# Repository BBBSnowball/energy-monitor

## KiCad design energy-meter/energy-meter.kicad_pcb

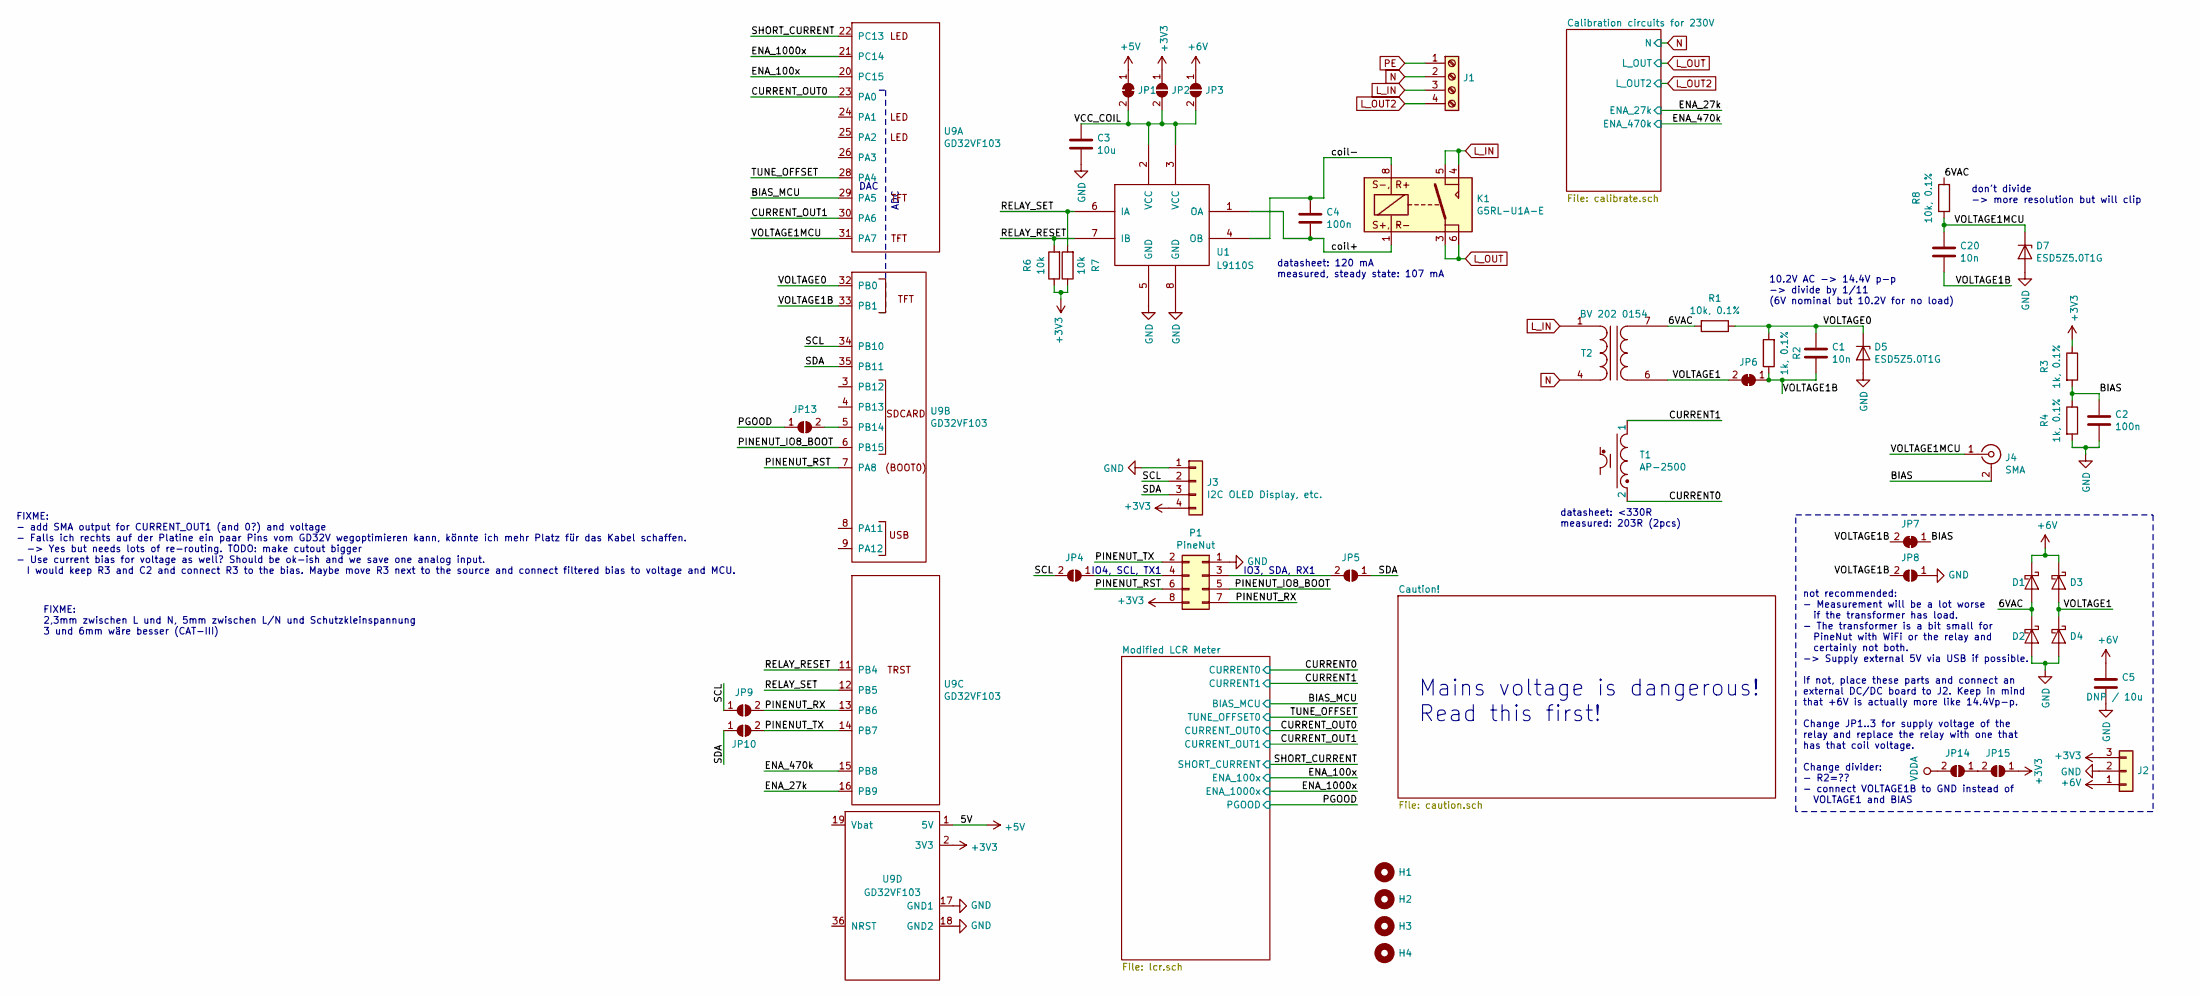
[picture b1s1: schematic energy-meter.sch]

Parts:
C1, C20: 10n; C_0603_1608Metric_Pad1.05x0.95mm_HandSolder
C2, C4: 100n; C_0603_1608Metric_Pad1.05x0.95mm_HandSolder
C3: 10u; C_0805_2012Metric_Pad1.15x1.40mm_HandSolder; LCSC CL21A106KOQNNNE
C5: DNP / 10u; C_0805_2012Metric_Pad1.15x1.40mm_HandSolder; LCSC CL21A106KOQNNNE
D1, D2, D3, D4: D_Schottky; D_SMA_Handsoldering; LCSC C181203, C364270, C50645
D5, D7: ESD5Z5.0T1G; D_SOD-523
H1, H2, H3, H4: MountingHole_3.2mm_M3; LCSC C63426, C357575, C357368, C357589
J1: Screw_Terminal_01x04; DG35C-B-04P-13-200AH
J2: Conn_01x03; PinHeader_1x03_P2.54mm_Horizontal
J3: I2C OLED Display, etc.; PinHeader_1x04_P2.54mm_Horizontal
J4: SMA; SMA_Samtec_SMA-J-P-H-ST-EM1_EdgeMount; LCSC C496550, C530661, (C1509221)
JP1, JP6, JP7: SolderJumper_2_Bridged; SolderJumper-2_P1.3mm_Bridged_RoundedPad1.0x1.5mm
JP2, JP3, JP4, JP5, JP8, JP9, JP10, JP13, JP14, JP15: SolderJumper_2_Open; SolderJumper-2_P1.3mm_Open_RoundedPad1.0x1.5mm
K1: G5RL-U1A-E
P1: PineNut; Pinenut-01S
R1, R8: 10k, 0.1%; R_0603_1608Metric_Pad1.05x0.95mm_HandSolder
R2, R3, R4: 1k, 0.1%; R_0603_1608Metric_Pad1.05x0.95mm_HandSolder
R6, R7: 10k; R_0603_1608Metric_Pad1.05x0.95mm_HandSolder
T1: AP-2500
T2: BV 202 0154; BV202
U1: L9110S; SOP-8_3.76x4.96mm_P1.27mm; LCSC C725793, C513306, C85174
U9: GD32VF103; GD32VF103CBT6-Sipeed-Longan-Nano

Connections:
+3V3: J2.3, J3.4, JP2.1 (A), JP15.1 (A), P1.8, R3.1, R6.1, R7.1, U9.2 (3V3); also elsewhere on the board
+5V: JP1.1 (A), U9.1 (5V); also elsewhere on the board
+6V: C5.1, D1.1 (K), D3.1 (K), J2.1, JP3.1 (A)
/6VAC: D1.2 (A), D2.1 (K), R1.2, R8.1, T2.7 (SB)
/BIAS: C2.1, J4.2 (Ext), JP7.1 (A), R3.2, R4.1
/BIAS_MCU: U9.29 (PA5); also elsewhere on the board
/CURRENT0: T1.2; also elsewhere on the board
/CURRENT1: T1.1; also elsewhere on the board
/CURRENT_OUT0: U9.23 (PA0); also elsewhere on the board
/CURRENT_OUT1: U9.30 (PA6); also elsewhere on the board
/ENA_27k: U9.16 (PB9); also elsewhere on the board
/ENA_100x: U9.20 (PC15); also elsewhere on the board
/ENA_470k: U9.15 (PB8); also elsewhere on the board
/ENA_1000x: U9.21 (PC14); also elsewhere on the board
/PGOOD: JP13.1 (A); also elsewhere on the board
/PINENUT_IO8_BOOT: P1.5, U9.6 (PB15)
/PINENUT_RST: P1.6, U9.7 (PA8)
/PINENUT_RX: JP9.2 (B), P1.7, U9.13 (PB6)
/PINENUT_TX: JP10.2 (B), P1.2, U9.14 (PB7)
/RELAY_RESET: R6.2, U1.7 (IB), U9.11 (PB4)
/RELAY_SET: R7.2, U1.6 (IA), U9.12 (PB5)
/SCL: J3.2, JP4.2 (B), JP9.1 (A), U9.34 (PB10); also elsewhere on the board
/SDA: J3.3, JP5.1 (A), JP10.1 (A), U9.35 (PB11); also elsewhere on the board
/SHORT_CURRENT: U9.22 (PC13); also elsewhere on the board
/TUNE_OFFSET: U9.28 (PA4); also elsewhere on the board
/VCC_COIL: C3.1, JP1.2 (B), JP2.2 (B), JP3.2 (B), U1.2 (VCC), U1.3 (VCC)
/VOLTAGE0: C1.1, D5.1 (K), R1.1, R2.2, U9.32 (PB0)
/VOLTAGE1: D3.2 (A), D4.1 (K), JP6.2 (B), T2.6 (SA)
/VOLTAGE1B: C1.2, C20.2, JP6.1 (A), JP7.2 (B), JP8.2 (B), R2.1, U9.33 (PB1)
/VOLTAGE1MCU: C20.1, D7.1 (K), J4.1 (In), R8.2, U9.31 (PA7)
/coil+: C4.2, K1.1, U1.1 (OA)
/coil-: C4.1, K1.8, U1.4 (OB)
GND: C2.2, C3.2, C5.2, D2.2 (A), D4.2 (A), D5.2 (A), D7.2 (A), J2.2, J3.1, JP8.1 (A), P1.1, R4.2, U1.5 (GND), U1.8 (GND), U9.17 (GND1), U9.18 (GND2); also elsewhere on the board
L_IN: J1.3, K1.4, K1.5, T2.1 (AA)
L_OUT: K1.3, K1.6; also elsewhere on the board
L_OUT2: J1.4; also elsewhere on the board
N: J1.2, T2.4 (AB); also elsewhere on the board
unnamed: JP4.1 (A), P1.4
unnamed: JP5.2 (B), P1.3
unnamed: JP13.2 (B), U9.5 (PB14)
unnamed: JP14.1 (A), JP15.2 (B)
PE: J1.1
VDDA: JP14.2 (B); also elsewhere on the board

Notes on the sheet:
ADC
IO3, SDA, RX1
IO4, SCL, TX1
10.2V AC -> 14.4V p-p -> divide by 1/11 (6V nominal but 10.2V for no load)
not recommended: - Measurement will be a lot worse if the transformer has load. - The transformer is a bit small for PineNut with WiFi or the relay and certainly not both. -> Supply external 5V via USB if possible. If not, place these parts and connect an external DC/DC board to J2. Keep in mind th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
DAC
datasheet: 120 mA measured, steady state: 107 mA
datasheet: <330R measured: 203R (2pcs)
Mains voltage is dangerous! Read this first!
don't divide -> more resolution but will clip
FIXME: - add SMA output for CURRENT_OUT1 (and 0?) and voltage - Falls ich rechts auf der Platine ein paar Pins vom GD32V wegoptimieren kann, könnte ich mehr Platz für das Kabel schaffen. -> Yes but needs lots of re-routing. TODO: make cutout bigger - Use current bias for voltage as well? Should be 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
FIXME: 2,3mm zwischen L und N, 5mm zwischen L/N und Schutzkleinspannung 3 und 6mm wäre besser (CAT-III)

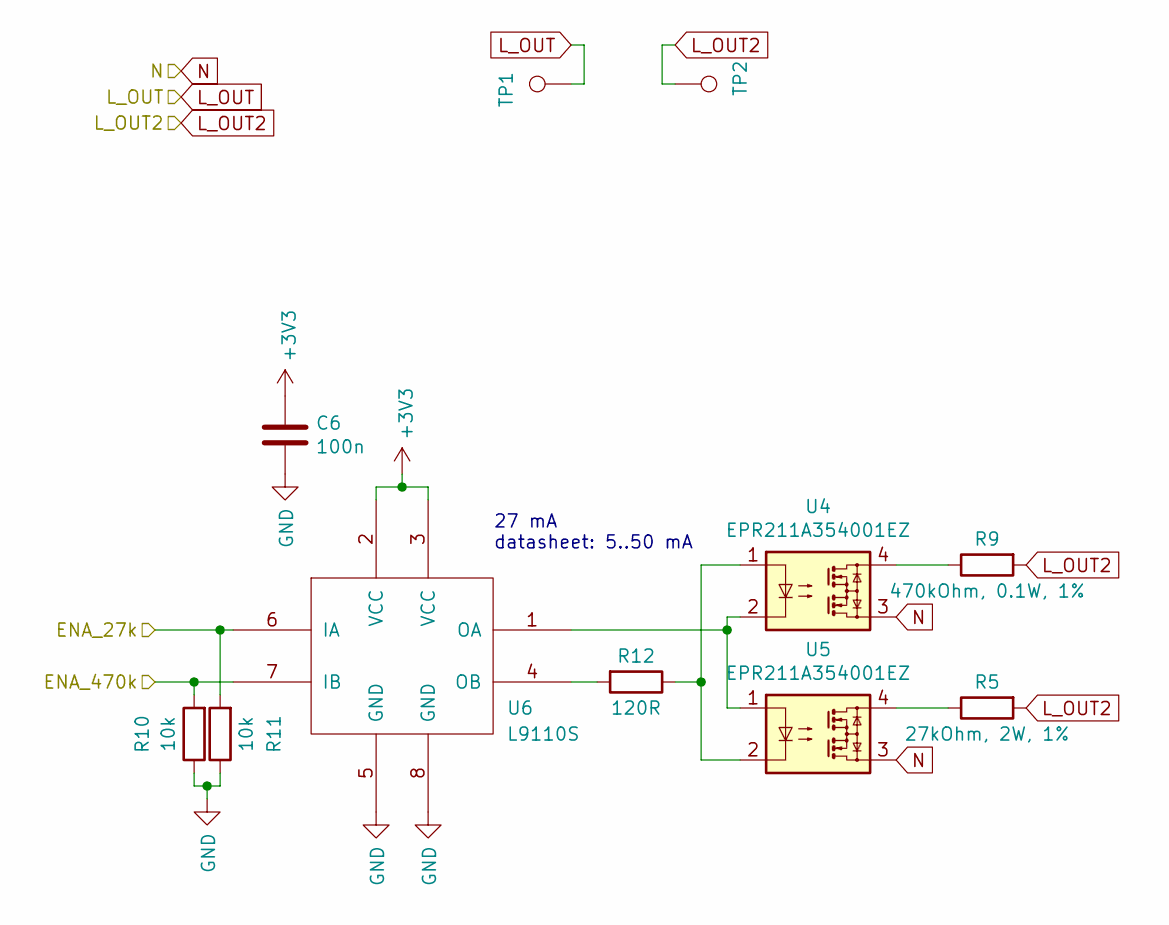
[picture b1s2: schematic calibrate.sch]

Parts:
C6: 100n; C_0603_1608Metric_Pad1.05x0.95mm_HandSolder
R5: 27kOhm, 2W, 1%; R_2512_6332Metric_Pad1.52x3.35mm_HandSolder
R9: 470kOhm, 0.1W, 1%; R_2512_6332Metric_Pad1.52x3.35mm_HandSolder
R10, R11: 10k; R_0603_1608Metric_Pad1.05x0.95mm_HandSolder
R12: 120R; R_0603_1608Metric_Pad1.05x0.95mm_HandSolder
TP1, TP2: TestPoint; TestPoint_THTPad_D4.0mm_Drill2.0mm
U4, U5: EPR211A354001EZ; DIP-4_W7.62mm
U6: L9110S; SOP-8_3.76x4.96mm_P1.27mm; LCSC C725793, C513306, C85174

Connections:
+3V3: C6.1, U6.2 (VCC), U6.3 (VCC); also elsewhere on the board
/ENA_27k: R11.2, U6.6 (IA); also elsewhere on the board
/ENA_470k: R10.2, U6.7 (IB); also elsewhere on the board
GND: C6.2, R10.1, R11.1, U6.5 (GND), U6.8 (GND); also elsewhere on the board
L_OUT: TP1.1; also elsewhere on the board
L_OUT2: R5.2, R9.2, TP2.1; also elsewhere on the board
N: U4.3, U5.3; also elsewhere on the board
unnamed: R5.1, U5.4
unnamed: R9.1, U4.4
unnamed: R12.1, U4.1, U5.2
unnamed: R12.2, U6.4 (OB)
unnamed: U4.2, U5.1, U6.1 (OA)

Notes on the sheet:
27 mA datasheet: 5..50 mA

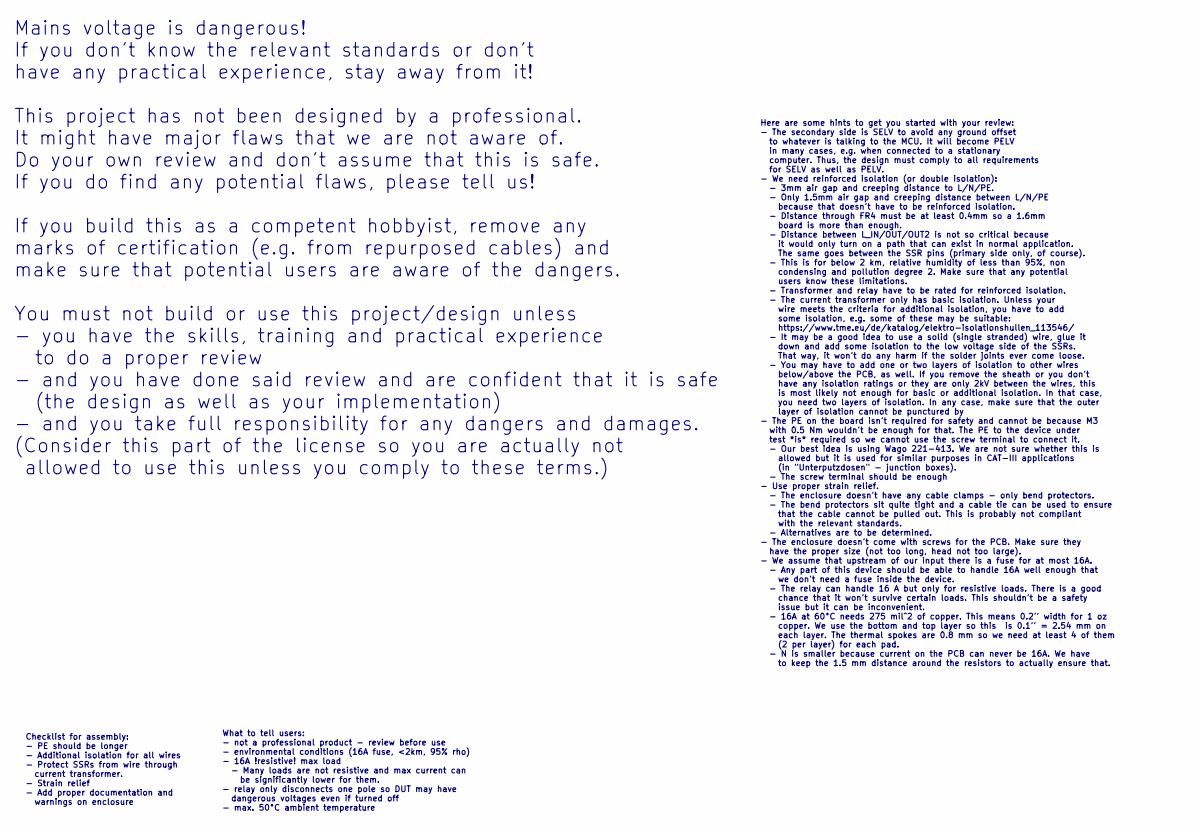
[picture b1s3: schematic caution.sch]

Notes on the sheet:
Mains voltage is dangerous! If you don't know the relevant standards or don't have any practical experience, stay away from it! This project has not been designed by a professional. It might have major flaws that we are not aware of. Do your own review and don't assume that this is safe. If you do 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
Here are some hints to get you started with your review: - The secondary side is SELV to avoid any ground offset to whatever is talking to the MCU. It will become PELV in many cases, e.g. when connected to a stationary computer. Thus, the design must comply to all requirements for SELV as well as P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
Checklist for assembly: - PE should be longer - Additional isolation for all wires - Protect SSRs from wire through current transformer. - Strain relief - Add proper documentation and warnings on enclosure
What to tell users: - not a professional product - review before use - environmental conditions (16A fuse, <2km, 95% rho) - 16A !resistive! max load - Many loads are not resistive and max current can be significantly lower for them. - relay only disconnects one pole so DUT may have dangerous voltag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

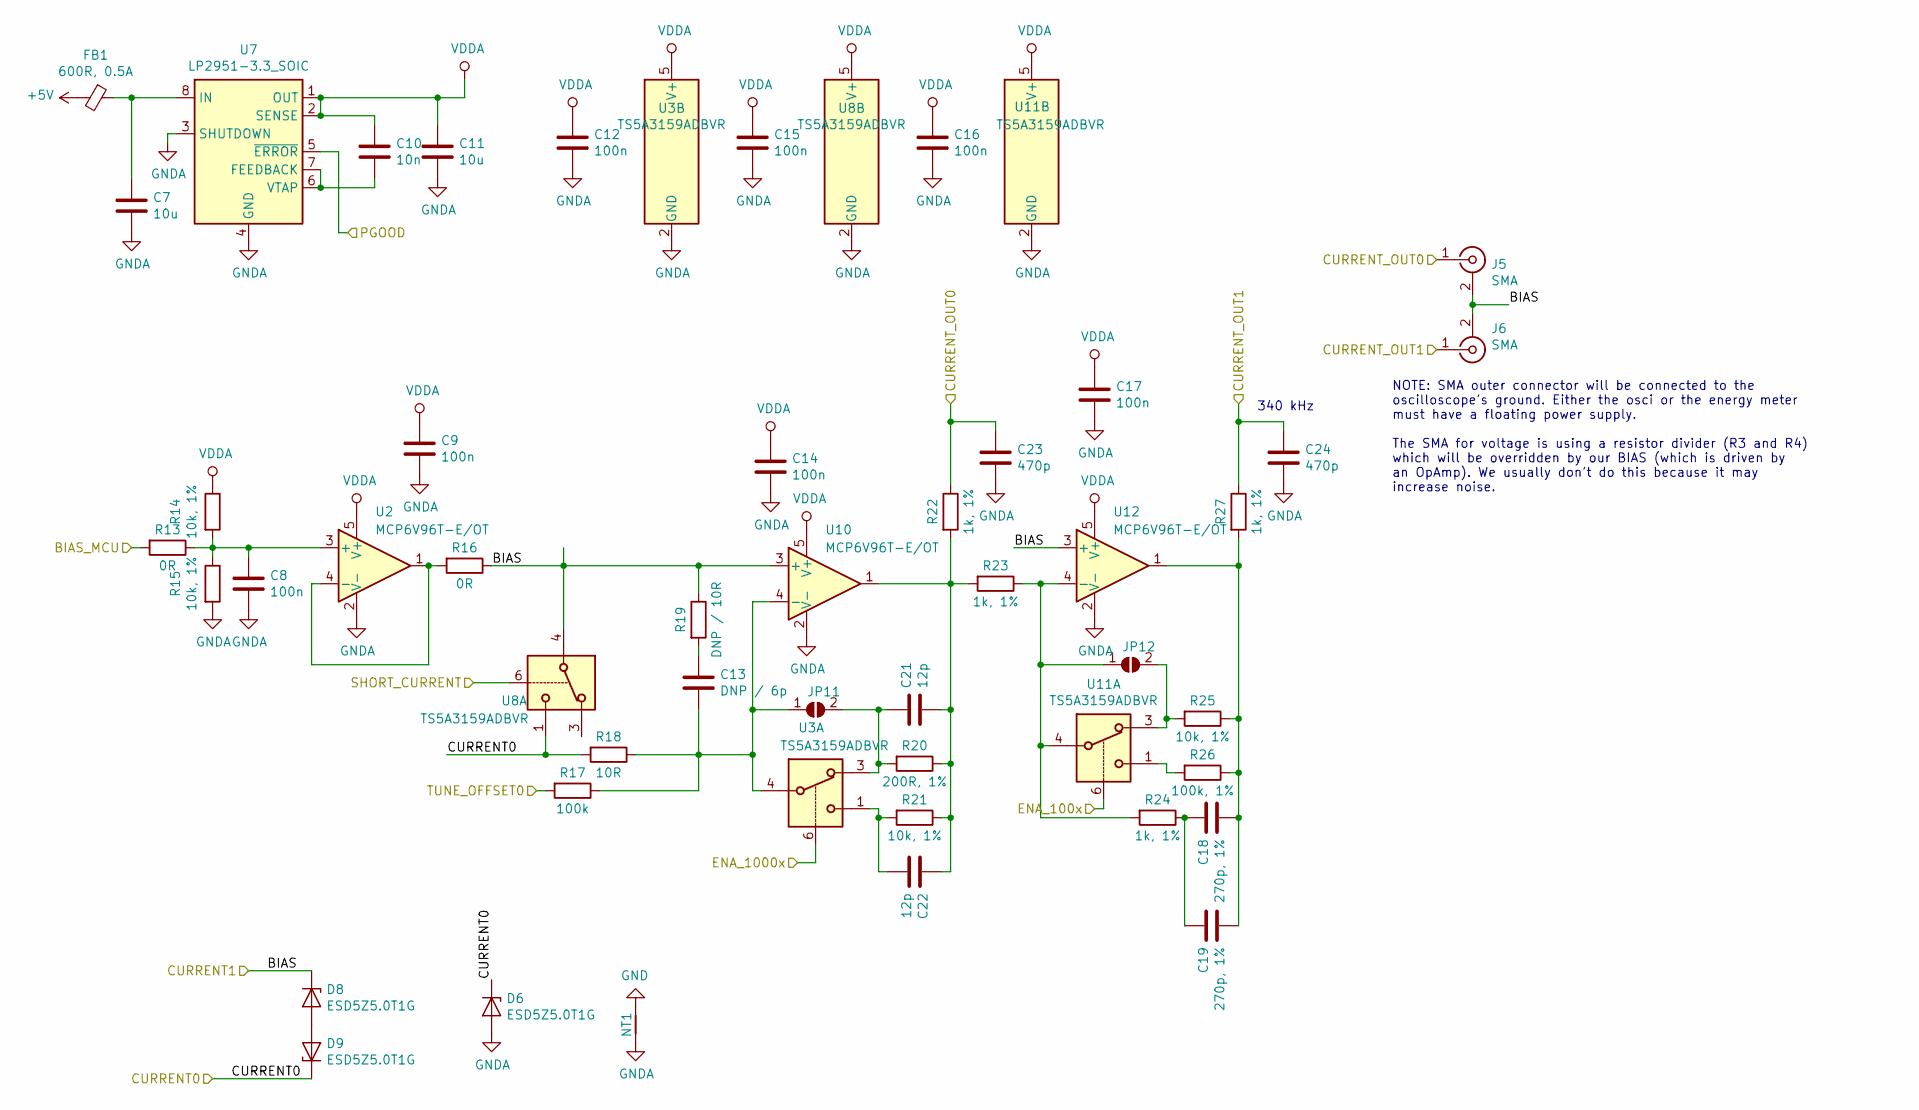
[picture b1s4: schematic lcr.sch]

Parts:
C7, C11: 10u; C_0805_2012Metric_Pad1.15x1.40mm_HandSolder; LCSC CL21A106KOQNNNE
C8, C9, C12, C14, C15, C16, C17: 100n; C_0603_1608Metric_Pad1.05x0.95mm_HandSolder
C10: 10n; C_0603_1608Metric_Pad1.05x0.95mm_HandSolder
C13: DNP / 6p; C_0603_1608Metric_Pad1.05x0.95mm_HandSolder
C18, C19: 270p, 1%; C_0603_1608Metric_Pad1.05x0.95mm_HandSolder
C21, C22: 12p; C_0603_1608Metric_Pad1.05x0.95mm_HandSolder
C23, C24: 470p; C_0603_1608Metric_Pad1.05x0.95mm_HandSolder
D6, D8, D9: ESD5Z5.0T1G; D_SOD-523
FB1: 600R, 0.5A; L_0603_1608Metric_Pad1.05x0.95mm_HandSolder; MPN BLM15PX601SZ1D
J5, J6: SMA; SMA_Samtec_SMA-J-P-H-ST-EM1_EdgeMount; LCSC C496550, C530661, (C1509221)
JP11, JP12: SolderJumper_2_Open; SolderJumper-2_P1.3mm_Open_RoundedPad1.0x1.5mm
NT1: Net-Tie_2; NetTie-2_SMD_Pad2.0mm
R13, R16: 0R; R_0603_1608Metric_Pad1.05x0.95mm_HandSolder
R14, R15, R21, R25: 10k, 1%; R_0603_1608Metric_Pad1.05x0.95mm_HandSolder
R17: 100k; R_0603_1608Metric_Pad1.05x0.95mm_HandSolder
R18: 10R; R_0603_1608Metric_Pad1.05x0.95mm_HandSolder
R19: DNP / 10R; R_0603_1608Metric_Pad1.05x0.95mm_HandSolder
R20: 200R, 1%; R_0603_1608Metric_Pad1.05x0.95mm_HandSolder
R22, R23, R24, R27: 1k, 1%; R_0603_1608Metric_Pad1.05x0.95mm_HandSolder
R26: 100k, 1%; R_0603_1608Metric_Pad1.05x0.95mm_HandSolder
U2, U10, U12: MCP6V96T-E/OT; SOT-23-5
U3, U8, U11: TS5A3159ADBVR; SOT-23-6
U7: LP2951-3.3_SOIC; SOIC-8_3.9x4.9mm_P1.27mm

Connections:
+5V: FB1.2; also elsewhere on the board
/BIAS_MCU: R13.2; also elsewhere on the board
/CURRENT0: D6.1 (K), D9.1 (K), R18.2, U8.1; also elsewhere on the board
/CURRENT1: D8.1 (K), J5.2 (Ext), J6.2 (Ext), R16.1, R19.1, U8.4, U10.3 (+), U12.3 (+); also elsewhere on the board
/CURRENT_OUT0: C23.1, J5.1 (In), R22.1; also elsewhere on the board
/CURRENT_OUT1: C24.1, J6.1 (In), R27.1; also elsewhere on the board
/ENA_100x: U11.6; also elsewhere on the board
/ENA_1000x: U3.6; also elsewhere on the board
/PGOOD: U7.5 (~ERROR); also elsewhere on the board
/SHORT_CURRENT: U8.6; also elsewhere on the board
/TUNE_OFFSET: R17.2; also elsewhere on the board
GND: NT1.1; also elsewhere on the board
GNDA: C7.2, C8.2, C9.2, C11.2, C12.2, C14.2, C15.2, C16.2, C17.2, C23.2, C24.2, D6.2 (A), NT1.2, R15.2, U2.2 (V-), U3.2 (GND), U7.3 (SHUTDOWN), U7.4 (GND), U8.2 (GND), U10.2 (V-), U11.2 (GND), U12.2 (V-)
unnamed: C7.1, FB1.1, U7.8 (IN)
unnamed: C8.1, R13.1, R14.2, R15.1, U2.3 (+)
unnamed: C10.2, U7.6 (VTAP), U7.7 (FEEDBACK)
unnamed: C13.1, R19.2
unnamed: C13.2, JP11.1 (A), R17.1, R18.1, U3.4, U10.4 (-)
unnamed: C18.1, C19.1, R24.1
unnamed: C18.2, C19.2, R25.1, R26.1, R27.2, U12.1
unnamed: C21.1, JP11.2 (B), R20.2, U3.3
unnamed: C21.2, C22.1, R20.1, R21.1, R22.2, R23.2, U10.1
unnamed: C22.2, R21.2, U3.1
unnamed: D8.2 (A), D9.2 (A)
unnamed: JP12.1 (A), R23.1, R24.2, U11.4, U12.4 (-)
unnamed: JP12.2 (B), R25.2, U11.3
unnamed: R16.2, U2.1, U2.4 (-)
unnamed: R26.2, U11.1
VDDA: C9.1, C10.1, C11.1, C12.1, C14.1, C15.1, C16.1, C17.1, R14.1, U2.5 (V+), U3.5 (V+), U7.1 (OUT), U7.2 (SENSE), U8.5 (V+), U10.5 (V+), U11.5 (V+), U12.5 (V+); also elsewhere on the board

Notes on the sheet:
340 kHz
NOTE: SMA outer connector will be connected to the oscilloscope's ground. Either the osci or the energy meter must have a floating power supply. The SMA for voltage is using a resistor divider (R3 and R4) which will be overridden by our BIAS (which is driven by an OpAmp). We usually don't do this b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

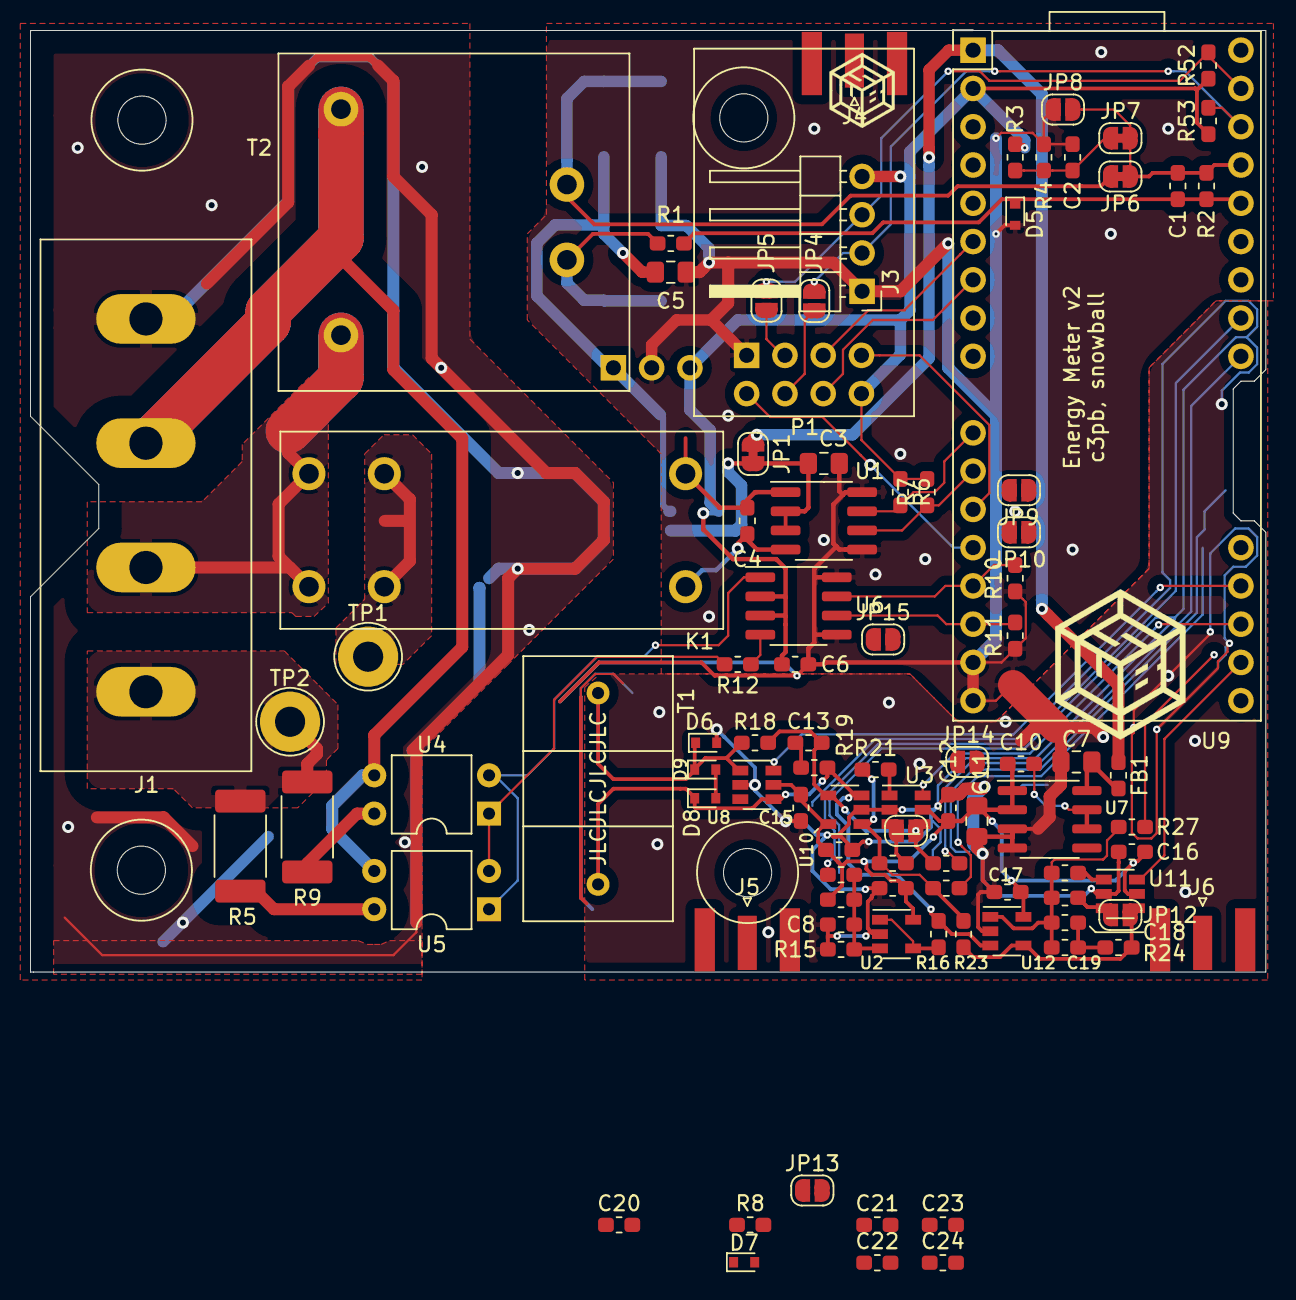
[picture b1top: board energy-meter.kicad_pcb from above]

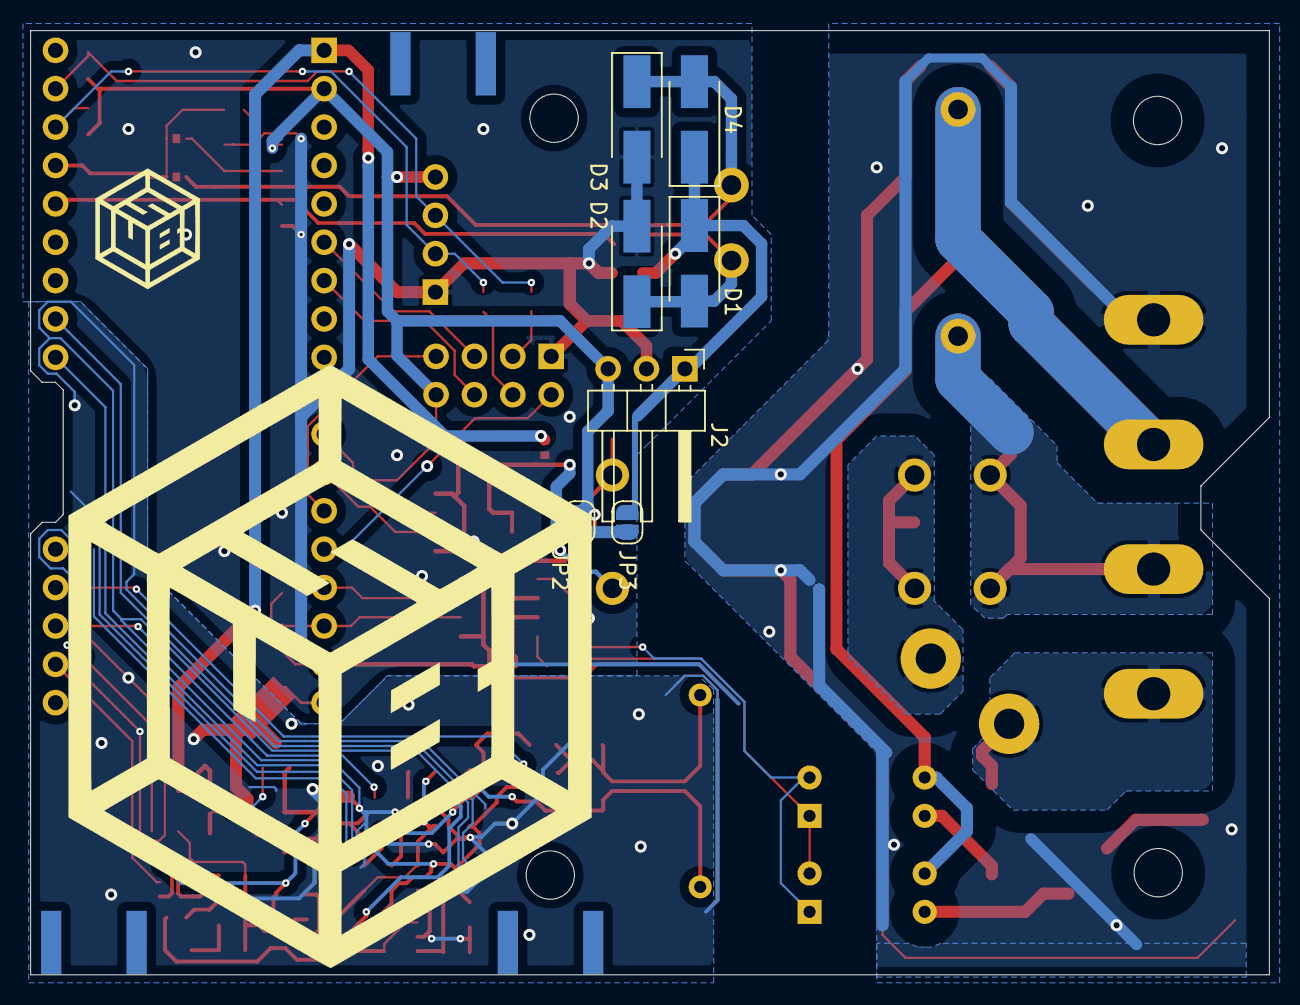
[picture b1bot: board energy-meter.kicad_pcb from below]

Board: 2 copper layers, 82.0 x 62.5 mm, 107 parts (7 on the bottom side), 63 nets.

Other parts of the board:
R52, R53: 10k; R_0603_1608Metric_Pad1.05x0.95mm_HandSolder

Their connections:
+3V3: R52.1, R53.1; also elsewhere on the board
/SCL: R53.2; also elsewhere on the board
/SDA: R52.2; also elsewhere on the board

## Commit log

2021-04-17 continue changing schematic
2021-04-17 remove two of the opamps
    We can measure the voltage without an amplifier so let's do it. The other
    was used for the LCR outputs, which we don't have here.
2021-04-17 everything done except current measurement
2021-04-17 DRC, add header for I2C
2021-04-17 add alternative relay
2021-04-17 move some text
2021-04-17 add optional internal load resistor
    This may be useful for calibration and tests.
2021-04-17 2nd relay needs an additional driver if we want to use both of them
2021-04-17 add some vias for PE
2021-04-18 adjust voltage divider to somewhat work if transformer is also used for VCC
    In that case, we will only see one half of the wave.
2021-04-18 use solid state relays for calibration
    That way, we have enough space for two of them. The alternative relay
    shares space with the other relay because only one of them will be used.
2021-04-18 add opamps
2021-04-18 add LTSpice files
2021-04-18 add logos, increase distance to SELV, add PDFs and Gerbers
    Lot's of whitespace changes, unfortunately.
2021-06-08 try capacitor in feedback of transimpedance amplifier -> seems to be a good idea
2021-06-08 add small circuit for measuring 230V with a Red Pitaya
2021-06-08 add some comments about isolation and standards compliance
2021-06-08 open files on Windows, add comment
2021-06-09 add sheet with warnings and design info
2021-06-09 remove optional parts, increase distance between conductors on primary side
2021-06-09 increase size of test points for wire through current transformer, unswap RELAY_SET/RESET
2021-06-09 handle most TODOs in schematic, PCB to be done
2021-06-09 fixups
2021-06-09 add cache libs
    Glowstone libraries are not published, yet. Therefore, the cache libraries
    are essential and it's a good idea in general.
2022-12-10 old changes
2022-12-10 fix two incomplete sentences
